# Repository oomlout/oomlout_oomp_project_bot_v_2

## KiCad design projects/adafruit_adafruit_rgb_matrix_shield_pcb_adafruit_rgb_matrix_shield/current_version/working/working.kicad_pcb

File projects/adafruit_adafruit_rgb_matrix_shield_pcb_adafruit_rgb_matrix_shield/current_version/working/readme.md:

# adafruit_rgb_matrix_shield_pcb
 
## summary 
* id: adafruit_adafruit_rgb_matrix_shield_pcb_adafruit_rgb_matrix_shield
* user: adafruit
* name: adafruit_rgb_matrix_shield_pcb
* board: adafruit_rgb_matrix_shield
* repo: https://github.com/adafruit/Adafruit-RGB-Matrix-Shield-PCB

* src_file_repo_sch: 
* src_file_repo_sch_link: https://github.com/adafruit/Adafruit-RGB-Matrix-Shield-PCB/tree/master/
* full details link: https://github.com/oomlout/oomlout_oomp_project_bot_v_2/tree/main/projects/adafruit_adafruit_rgb_matrix_shield_pcb_adafruit_rgb_matrix_shield/current_version/working  

## schematic  
  
[schematic (pdf)](working_schematic.pdf) 

## pcb  

[board (pdf)](working.pdf)  

## working_bom
| Id | Designator | Footprint | Quantity | Designation | Supplier and ref |  | None | 
| --- | --- | --- | --- | --- | --- | --- | --- | 
| 1 | SJ2,SJ6,SJ14,SJ13,SJ12,SJ10,SJ7,SJ3,SJ5,SJ4,SJ9,SJ8,SJ1 | SOLDERJUMPER_CLOSEDWIRE | 13 |  |  |  | [''] | 
| 2 | JP1,JP4 | 1X08-CLEANBIG | 2 |  |  |  | [''] | 
| 3 | U$9 | ADAFRUIT_TEXT_20MM | 1 |  |  |  | [''] | 
| 4 | S4 | B3F-10XX | 1 | 6mm |  |  | [''] | 
| 5 | JP15 | 2X08_SHROUDED | 1 | Shrouded 2x8 |  |  | [''] | 
| 6 | JP3,JP2 | 1X08_ROUND_76 | 2 |  |  |  | [''] | 
| 7 | @HOLE1,@HOLE0,@HOLE2 |  | 3 |  |  |  | [''] | 
| 8 | U$8 | PCBFEAT-REV-040 | 1 |  |  |  | [''] | 
| 9 | JP6 | 1X10_ROUND70 | 1 |  |  |  | [''] | 
| 10 | MATRIX_PWR0 | TERMBLOCK508 | 1 | PINHEAD |  |  | [''] | 
| 11 | U$41 | ARDUINOR3_ICSP_NODIM | 1 | ARDUINO_R3_ICSP_NODIM |  |  | [''] | 
| 12 | JP8 | 1X06-CLEANBIG | 1 |  |  |  | [''] | 

## bom_schematic
| Ref | Qnty | Value | Cmp name | Footprint | Description | Vendor | DNP | 
| --- | --- | --- | --- | --- | --- | --- | --- | 
| JP1, JP4 | 2 | PINHD-1X8CLEANBIG | PINHD-1X8CLEANBIG | working:1X08-CLEANBIG |  |  |  | 
| JP2, JP3 | 2 | HEADER-1X876MIL | HEADER-1X876MIL | working:1X08_ROUND_76 |  |  |  | 
| JP6 | 1 | HEADER-1X1070MIL | HEADER-1X1070MIL | working:1X10_ROUND70 |  |  |  | 
| JP8 | 1 | PINHD-1X6CB | PINHD-1X6CB | working:1X06-CLEANBIG |  |  |  | 
| JP15 | 1 | Shrouded 2x8 | HEADER-2X8_SHROUDED | working:2X08_SHROUDED |  |  |  | 
| MATRIX_PWR0 | 1 | PINHEAD | PINHEAD | working:TERMBLOCK508 |  |  |  | 
| S4 | 1 | 6mm | 10-XX | working:B3F-10XX |  |  |  | 
| SJ1, SJ2, SJ3, SJ4, SJ5, SJ6, SJ7, SJ8, SJ9, SJ10, SJ12, SJ13, SJ14 | 13 | SOLDERJUMPERCLOSED | SOLDERJUMPERCLOSED | working:SOLDERJUMPER_CLOSEDWIRE |  |  |  | 
| U$41 | 1 | ARDUINO_R3_ICSP_NODIM | ARDUINO_R3_ICSP_NODIM | working:ARDUINOR3_ICSP_NODIM |  |  |  |

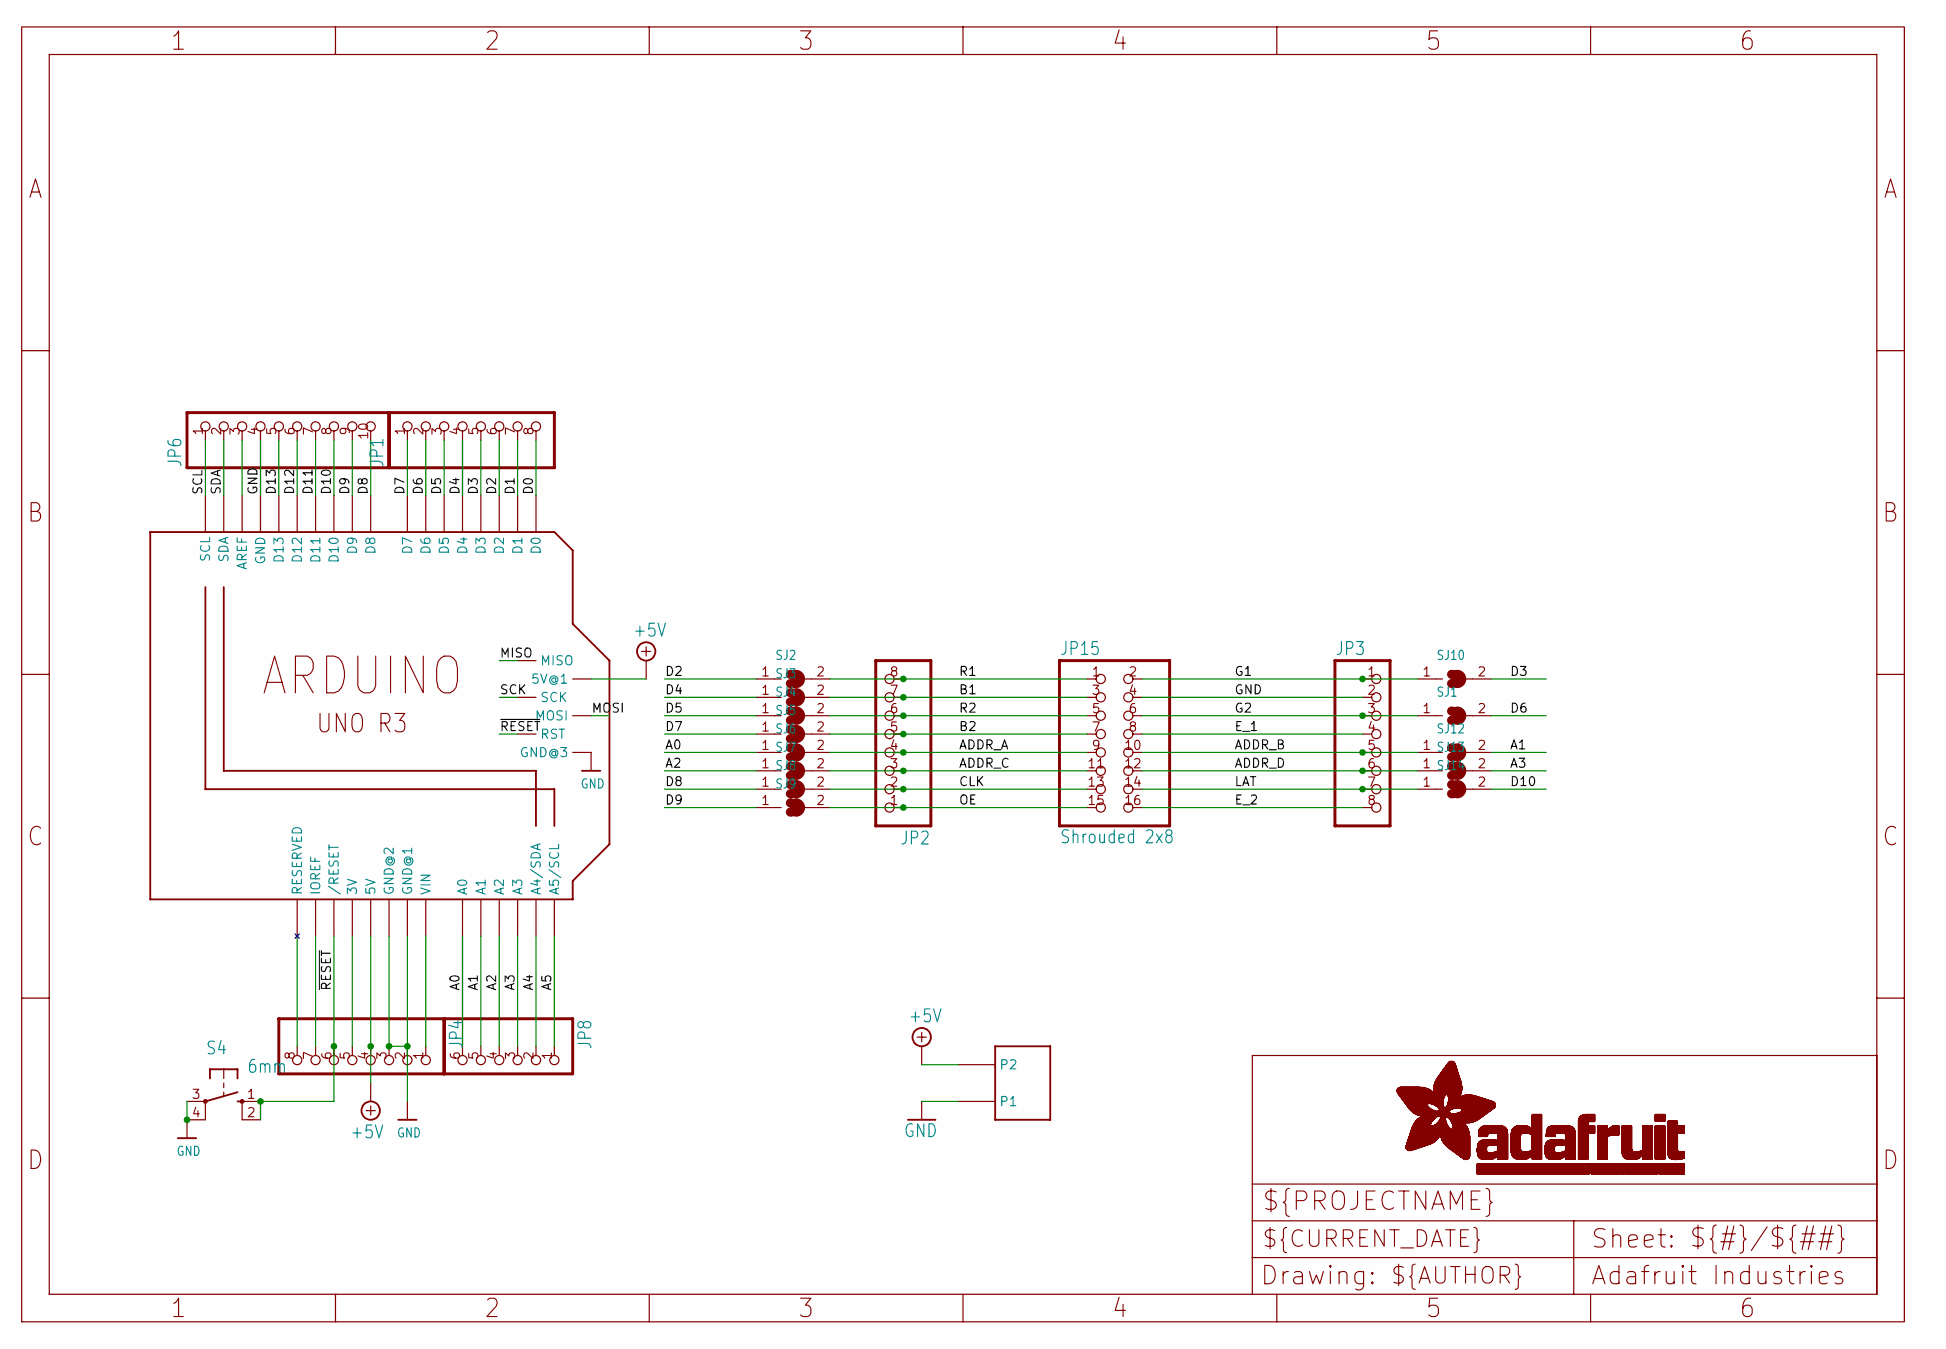
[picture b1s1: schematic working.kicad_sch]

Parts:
JP1, JP4: PINHD-1X8CLEANBIG; 1X08-CLEANBIG
JP2, JP3: HEADER-1X876MIL; 1X08_ROUND_76
JP6: HEADER-1X1070MIL; 1X10_ROUND70
JP8: PINHD-1X6CB; 1X06-CLEANBIG
JP15: Shrouded 2x8; 2X08_SHROUDED
MATRIX_PWR0: PINHEAD; TERMBLOCK508
S4: 6mm; B3F-10XX
SJ1, SJ2, SJ3, SJ4, SJ5, SJ6, SJ7, SJ8, SJ9, SJ10, SJ12, SJ13, SJ14: SOLDERJUMPERCLOSED; SOLDERJUMPER_CLOSEDWIRE
U$41: ARDUINO_R3_ICSP_NODIM; ARDUINOR3_ICSP_NODIM

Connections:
+3V: JP4.5, U$41.3V
+5V: JP4.4, MATRIX_PWR0.P$4 (P2), U$41.5V, U$41.5V_ICSP (5V@1)
A0: JP8.6, SJ6.1, U$41.A0
A1: JP8.5, SJ12.2, U$41.A1
A2: JP8.4, SJ7.1, U$41.A2
A3: JP8.3, SJ13.2, U$41.A3
A4: JP8.2, U$41.A4 (A4/SDA)
A5: JP8.1, U$41.A5 (A5/SCL)
ADDR_A: JP2.4, JP15.9, SJ6.2
ADDR_B: JP3.5, JP15.10, SJ12.1
ADDR_C: JP2.3, JP15.11, SJ7.2
ADDR_D: JP3.6, JP15.12, SJ13.1
AREF: JP6.3, U$41.AREF
B1: JP2.7, JP15.3, SJ3.2
B2: JP2.5, JP15.7, SJ5.2
CLK: JP2.2, JP15.13, SJ8.2
D0: JP1.8, U$41.D0
D1: JP1.7, U$41.D1
D2: JP1.6, SJ2.1, U$41.D2
D3: JP1.5, SJ10.2, U$41.D3
D4: JP1.4, SJ3.1, U$41.D4
D5: JP1.3, SJ4.1, U$41.D5
D6: JP1.2, SJ1.2, U$41.D6
D7: JP1.1, SJ5.1, U$41.D7
D8: JP6.10, SJ8.1, U$41.D8
D9: JP6.9, SJ9.1, U$41.D9
D10: JP6.8, SJ14.2, U$41.D10
D11: JP6.7, U$41.D11
D12: JP6.6, U$41.D12
D13: JP6.5, U$41.D13
E_1: JP3.4, JP15.8
E_2: JP3.8, JP15.16
G1: JP3.1, JP15.2, SJ10.1
G2: JP3.3, JP15.6, SJ1.1
GND: JP3.2, JP4.2, JP4.3, JP6.4, JP15.4, MATRIX_PWR0.P$3 (P1), S4.3, S4.4 (P1), U$41.GND, U$41.GND@1 (GND@2), U$41.GND@2 (GND@3), U$41.GND@3 (GND@1)
IOREF: JP4.7, U$41.IOREF
LAT: JP3.7, JP15.14, SJ14.1
MISO: U$41.MISO
MOSI: U$41.MOSI
NC: JP4.8, U$41.RESERVED
OE: JP2.1, JP15.15, SJ9.2
R1: JP2.8, JP15.1, SJ2.2
R2: JP2.6, JP15.5, SJ4.2
SCK: U$41.SCK
SCL: JP6.1, U$41.SCL
SDA: JP6.2, U$41.SDA
VIN: JP4.1, U$41.VIN
~RESET: JP4.6, S4.1 (S), S4.2 (S1), U$41.RESET (/RESET), U$41.RESET_ICSP (RST)

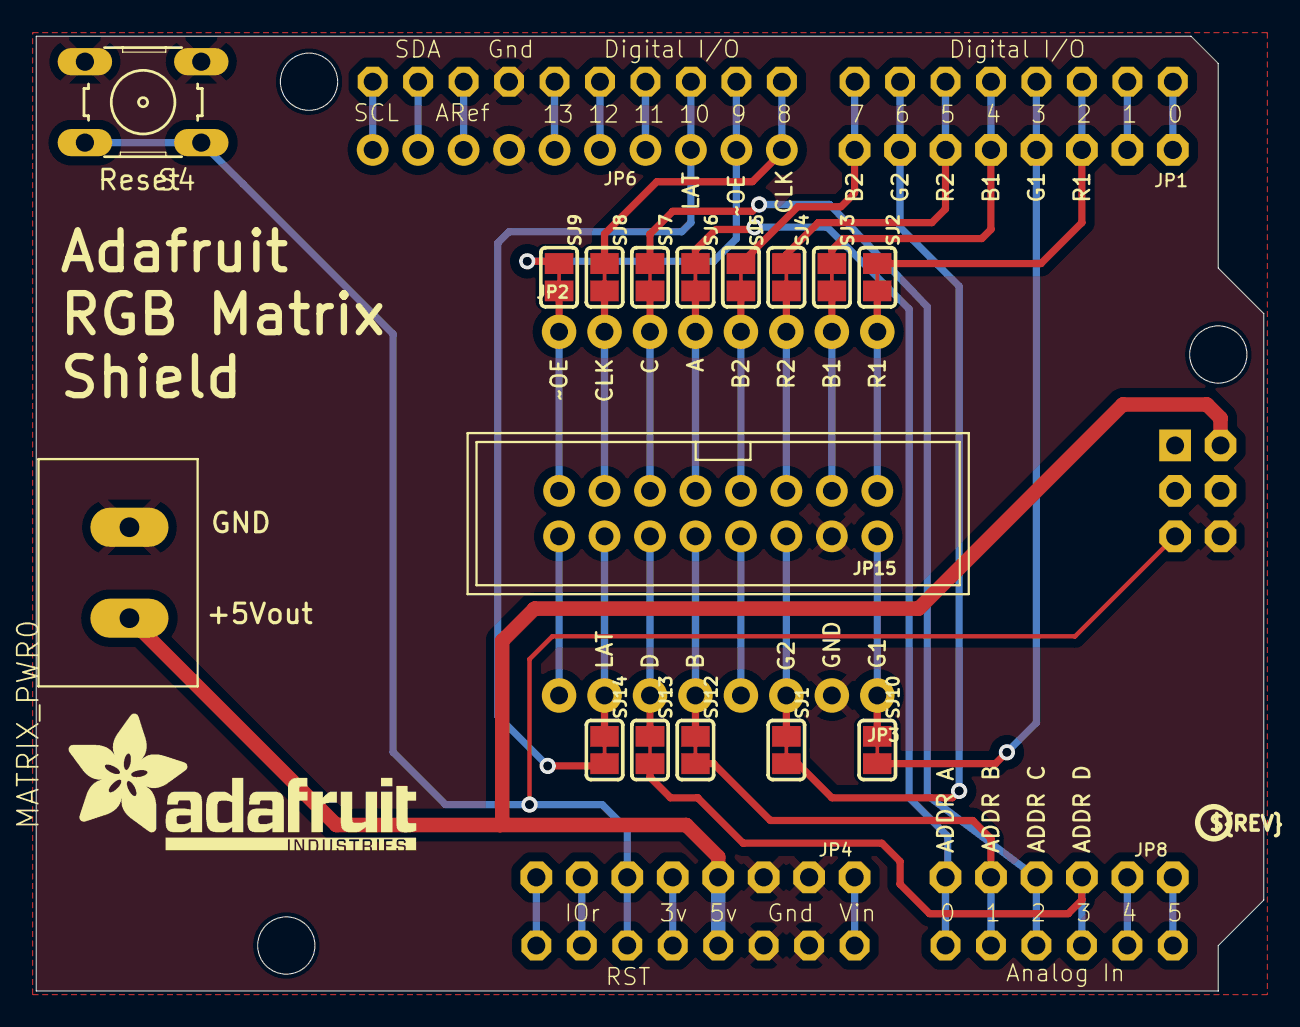
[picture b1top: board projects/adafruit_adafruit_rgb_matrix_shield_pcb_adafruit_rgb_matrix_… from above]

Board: 2 copper layers, 68.6 x 53.3 mm, 28 parts (0 on the bottom side), 45 nets.

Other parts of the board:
@HOLE0, @HOLE1, @HOLE2: (no value)
U$8: PCBFEAT-REV-040
U$9: ADAFRUIT_TEXT_20MM

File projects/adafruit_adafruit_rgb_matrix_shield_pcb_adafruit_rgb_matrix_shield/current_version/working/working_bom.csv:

"Id";"Designator";"Footprint";"Quantity";"Designation";"Supplier and ref";
1;"SJ2,SJ6,SJ14,SJ13,SJ12,SJ10,SJ7,SJ3,SJ5,SJ4,SJ9,SJ8,SJ1";"SOLDERJUMPER_CLOSEDWIRE";13;"";;;
2;"JP1,JP4";"1X08-CLEANBIG";2;"";;;
3;"U$9";"ADAFRUIT_TEXT_20MM";1;"";;;
4;"S4";"B3F-10XX";1;"6mm";;;
5;"JP15";"2X08_SHROUDED";1;"Shrouded 2x8";;;
6;"JP3,JP2";"1X08_ROUND_76";2;"";;;
7;"@HOLE1,@HOLE0,@HOLE2";"";3;"";;;
8;"U$8";"PCBFEAT-REV-040";1;"";;;
9;"JP6";"1X10_ROUND70";1;"";;;
10;"MATRIX_PWR0";"TERMBLOCK508";1;"PINHEAD";;;
11;"U$41";"ARDUINOR3_ICSP_NODIM";1;"ARDUINO_R3_ICSP_NODIM";;;
12;"JP8";"1X06-CLEANBIG";1;"";;;

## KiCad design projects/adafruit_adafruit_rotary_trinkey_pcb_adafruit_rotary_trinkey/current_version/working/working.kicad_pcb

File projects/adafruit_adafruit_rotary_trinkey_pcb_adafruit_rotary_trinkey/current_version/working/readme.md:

# adafruit_rotary_trinkey_pcb
 
## summary 
* id: adafruit_adafruit_rotary_trinkey_pcb_adafruit_rotary_trinkey
* user: adafruit
* name: adafruit_rotary_trinkey_pcb
* board: adafruit_rotary_trinkey
* repo: https://github.com/adafruit/Adafruit-Rotary-Trinkey-PCB

* src_file_repo_sch: 
* src_file_repo_sch_link: https://github.com/adafruit/Adafruit-Rotary-Trinkey-PCB/tree/main/
* full details link: https://github.com/oomlout/oomlout_oomp_project_bot_v_2/tree/main/projects/adafruit_adafruit_rotary_trinkey_pcb_adafruit_rotary_trinkey/current_version/working  

## schematic  
  
[schematic (pdf)](working_schematic.pdf) 

## pcb  

[board (pdf)](working.pdf)  

## working_bom
| Id | Designator | Footprint | Quantity | Designation | Supplier and ref |  | None | 
| --- | --- | --- | --- | --- | --- | --- | --- | 
| 1 | SW1 | PEC11+SWITCH | 1 | PEC11 |  |  | [''] | 
| 2 | CN1 | USBA_PCB | 1 |  |  |  | [''] | 
| 3 | TOUCH0 | TESTPOINT_PAD_1MM | 1 |  |  |  | [''] | 
| 4 | LED1 | SK6805_1515 | 1 | WS2812B_SK6805_1515 |  |  | [''] | 
| 5 | Q2 | BTN_KMR2_4.6X2.8 | 1 | reset |  |  | [''] | 
| 6 | C8,C3 | 0805-NO | 2 | 10uF |  |  | [''] | 
| 7 | IC3 | QFN32_5MM | 1 | ATSAMD21E |  |  | [''] | 
| 8 | RST0,SWD0,SWC0 | TP16R | 3 | TPTP16R |  |  | [''] | 
| 9 | U$5 | ADAFRUIT_9MM | 1 |  |  |  | [''] | 
| 10 | FID2,FID1 | FIDUCIAL_1MM | 2 | FIDUCIAL_1MM |  |  | [''] | 
| 11 | C4,C5 | 0603-NO | 2 | 1uF |  |  | [''] | 
| 12 | U$8 | PCBFEAT-REV-040 | 1 |  |  |  | [''] | 
| 13 | U1 | SOT23-5 | 1 | AP2112K-3.3 |  |  | [''] | 

## bom_schematic
| Ref | Qnty | Value | Cmp name | Footprint | Description | Vendor | DNP | 
| --- | --- | --- | --- | --- | --- | --- | --- | 
| C3, C8 | 2 | 10uF | CAP_CERAMIC0805-NOOUTLINE | working:0805-NO |  |  |  | 
| C4, C5 | 2 | 1uF | CAP_CERAMIC0603_NO | working:0603-NO |  |  |  | 
| CN1 | 1 | USB_TYPEAPCB | USB_TYPEAPCB | working:USBA_PCB |  |  |  | 
| FID1, FID2 | 2 | FIDUCIAL_1MM | FIDUCIAL_1MM | working:FIDUCIAL_1MM |  |  |  | 
| IC3 | 1 | ATSAMD21E | ATSAMD21E | working:QFN32_5MM |  |  |  | 
| LED1 | 1 | WS2812B_SK6805_1515 | WS2812B_SK6805_1515 | working:SK6805_1515 |  |  |  | 
| Q2 | 1 | reset | SWITCH_TACT_SMT4.6X2.8 | working:BTN_KMR2_4.6X2.8 |  |  |  | 
| RST0 | 1 | TPTP16R | TPTP16R | working:TP16R |  |  |  | 
| SW1 | 1 | PEC11 | ENCODER_PLUS_SWITCH_PEC11 | working:PEC11+SWITCH |  |  |  | 
| SWC0 | 1 | TPTP16R | TPTP16R | working:TP16R |  |  |  | 
| SWD0 | 1 | TPTP16R | TPTP16R | working:TP16R |  |  |  | 
| TOUCH0 | 1 | TESTPOINTPAD1MM | TESTPOINTPAD1MM | working:TESTPOINT_PAD_1MM |  |  |  | 
| U1 | 1 | AP2112K-3.3 | VREG_SOT23-5 | working:SOT23-5 |  |  |  |

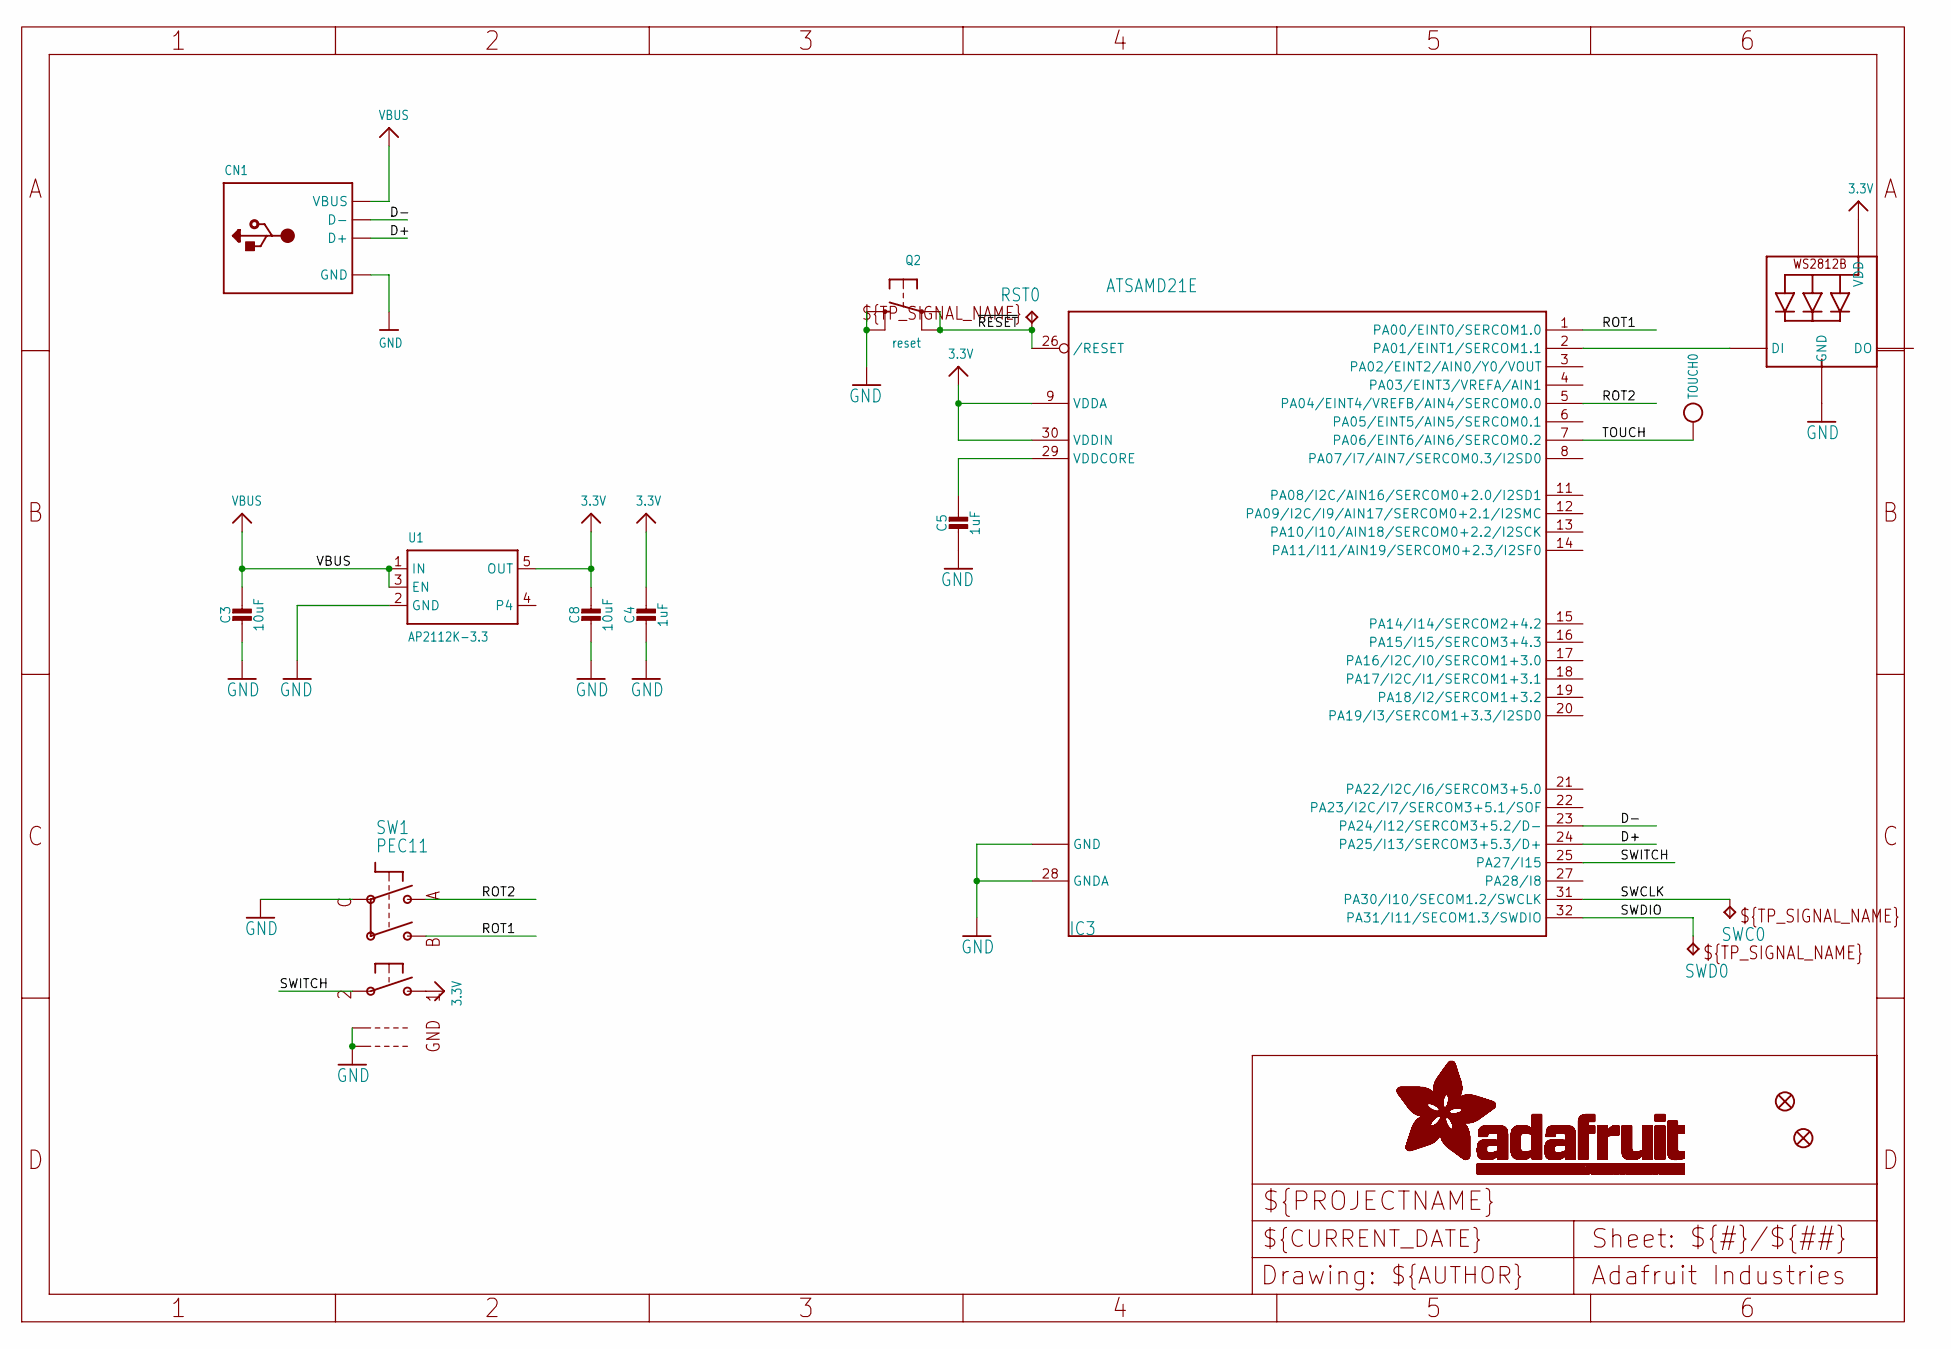
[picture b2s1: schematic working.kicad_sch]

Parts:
C3, C8: 10uF; 0805-NO
C4, C5: 1uF; 0603-NO
CN1: USB_TYPEAPCB; USBA_PCB
FID1, FID2: FIDUCIAL_1MM
IC3: ATSAMD21E; QFN32_5MM
LED1: WS2812B_SK6805_1515; SK6805_1515
Q2: reset; BTN_KMR2_4.6X2.8
RST0: TPTP16R; TP16R
SW1: PEC11; PEC11+SWITCH
SWC0: TPTP16R; TP16R
SWD0: TPTP16R; TP16R
TOUCH0: TESTPOINTPAD1MM; TESTPOINT_PAD_1MM
U1: AP2112K-3.3; SOT23-5

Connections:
3.3V: C4.1, C8.1, IC3.9 (VDDA), IC3.30 (VDDIN), LED1.2 (VDD), SW1.P$1, U1.5 (OUT)
D+: CN1.USB_PLUS (D+), IC3.24 (PA25/I13/SERCOM3+5.3/D+)
D-: CN1.USB_NEG (D-), IC3.23 (PA24/I12/SERCOM3+5.2/D-)
GND: C3.2, C4.2, C5.2, C8.2, CN1.GND, IC3.10 (GND), IC3.28 (GNDA), IC3.33 (GND), LED1.4 (GND), Q2.B (S), Q2.B' (S1), SW1.P$C, SW1.P$GND1, SW1.P$GND2, U1.2 (GND)
unnamed: IC3.2 (PA01/EINT1/SERCOM1.1), LED1.1 (DI)
ROT1: IC3.1 (PA00/EINT0/SERCOM1.0), SW1.P$B
ROT2: IC3.5 (PA04/EINT4/VREFB/AIN4/SERCOM0.0), SW1.P$A
SWCLK: IC3.31 (PA30/I10/SECOM1.2/SWCLK), SWC0.TP
SWDIO: IC3.32 (PA31/I11/SECOM1.3/SWDIO), SWD0.TP
SWITCH: IC3.25 (PA27/I15), SW1.P$2
TOUCH: IC3.7 (PA06/EINT6/AIN6/SERCOM0.2), TOUCH0.P$1
VBUS: C3.1, CN1.VCC (VBUS), U1.1 (IN), U1.3 (EN)
VDDCORE1: C5.1, IC3.29 (VDDCORE)
~RESET: IC3.26 (/RESET), Q2.A, Q2.A' (P1), RST0.TP

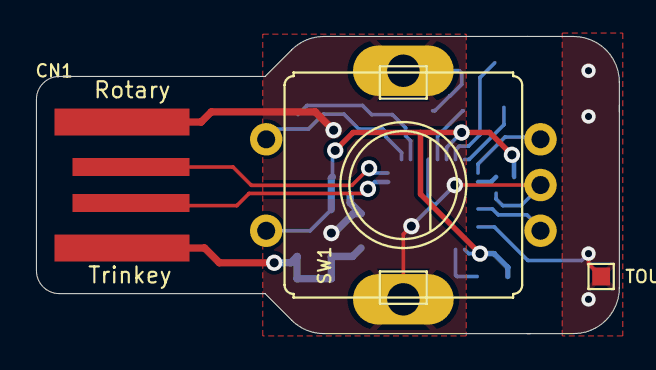
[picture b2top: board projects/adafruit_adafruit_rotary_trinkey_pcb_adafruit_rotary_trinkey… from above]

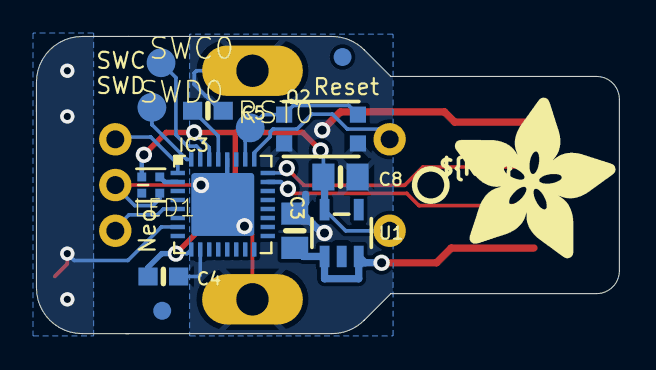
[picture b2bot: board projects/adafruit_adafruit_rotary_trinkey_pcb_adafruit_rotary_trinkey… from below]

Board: 2 copper layers, 32.4 x 16.5 mm, 18 parts (15 on the bottom side), 14 nets.

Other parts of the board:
U$5: ADAFRUIT_9MM
U$8: PCBFEAT-REV-040

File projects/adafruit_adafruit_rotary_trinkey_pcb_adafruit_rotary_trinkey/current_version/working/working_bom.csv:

"Id";"Designator";"Footprint";"Quantity";"Designation";"Supplier and ref";
1;"SW1";"PEC11+SWITCH";1;"PEC11";;;
2;"CN1";"USBA_PCB";1;"";;;
3;"TOUCH0";"TESTPOINT_PAD_1MM";1;"";;;
4;"LED1";"SK6805_1515";1;"WS2812B_SK6805_1515";;;
5;"Q2";"BTN_KMR2_4.6X2.8";1;"reset";;;
6;"C8,C3";"0805-NO";2;"10uF";;;
7;"IC3";"QFN32_5MM";1;"ATSAMD21E";;;
8;"RST0,SWD0,SWC0";"TP16R";3;"TPTP16R";;;
9;"U$5";"ADAFRUIT_9MM";1;"";;;
10;"FID2,FID1";"FIDUCIAL_1MM";2;"FIDUCIAL_1MM";;;
11;"C4,C5";"0603-NO";2;"1uF";;;
12;"U$8";"PCBFEAT-REV-040";1;"";;;
13;"U1";"SOT23-5";1;"AP2112K-3.3";;;

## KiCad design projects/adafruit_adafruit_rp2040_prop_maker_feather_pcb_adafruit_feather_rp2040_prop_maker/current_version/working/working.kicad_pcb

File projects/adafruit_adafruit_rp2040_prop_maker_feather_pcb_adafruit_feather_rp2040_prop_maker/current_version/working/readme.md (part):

# adafruit_rp2040_prop_maker_feather_pcb
 
## summary 
* id: adafruit_adafruit_rp2040_prop_maker_feather_pcb_adafruit_feather_rp2040_prop_maker
* user: adafruit
* name: adafruit_rp2040_prop_maker_feather_pcb
* board: adafruit_feather_rp2040_prop_maker
* repo: https://github.com/adafruit/Adafruit-RP2040-Prop-Maker-Feather-PCB

* src_file_repo_sch: 
* src_file_repo_sch_link: https://github.com/adafruit/Adafruit-RP2040-Prop-Maker-Feather-PCB/tree/main/
* full details link: https://github.com/oomlout/oomlout_oomp_project_bot_v_2/tree/main/projects/adafruit_adafruit_rp2040_prop_maker_feather_pcb_adafruit_feather_rp2040_prop_maker/current_version/working  

## schematic  
  
[schematic (pdf)](working_schematic.pdf) 

## pcb  

[board (pdf)](working.pdf)  

## working_bom
| Id | Designator | Footprint | Quantity | Designation | Supplier and ref |  | None | 
| --- | --- | --- | --- | --- | --- | --- | --- | 
| 1 | PLABEL30 | PLABEL30 | 1 |  |  |  | [''] | 
| 2 | R2,R5,R1,R4,R14,R3,R15,R7 | _0402NO | 8 | 10K |  |  | [''] | 
| 3 | C7,C6,C12,C18,C9,C13,C16,C14 | _0402NO | 8 | 0.1uF |  |  | [''] | 
| 4 | R6,R11 | _0402NO | 2 | 1K |  |  | [''] | 
| 5 | U$31,U$32 | MOUNTINGHOLE_2.5_PLATED | 2 | MOUNTINGHOLE2.5 |  |  | [''] | 
| 6 | C20,C1,C19,C5,C4 | 0805-NO | 5 | 10uF/16V |  |  | [''] | 
| 7 | PLABEL72 | PLABEL72 | 1 |  |  |  | [''] | 
| 8 | U$35,U$34 | FIDUCIAL_1MM | 2 | FIDUCIAL_1MM |  |  | [''] | 
| 9 | OUTPUTS0 | 1X06_OVAL | 1 | TERMINALS |  |  | [''] | 
| 10 | PLABEL13 | PLABEL13 | 1 |  |  |  | [''] | 
| 11 | LED1 | SK6805_1515 | 1 | WS2812B_SK6805_1515 |  |  | [''] | 
| 12 | PLABEL73 | PLABEL73 | 1 |  |  |  | [''] | 
| 13 | R19 | _0402NO | 1 | 100 |  |  | [''] | 
| 14 | PLABEL6 | PLABEL6 | 1 |  |  |  | [''] | 
| 15 | Y1 | CRYSTAL_2.5X2 | 1 | 12MHz/12pF |  |  | [''] | 
| 16 | PLABEL33 | PLABEL33 | 1 |  |  |  | [''] | 
| 17 | U2 | SOT23-5 | 1 | RT9080-3.3 |  |  | [''] | 
| 18 | R16,R17 | _0402NO | 2 | 100K |  |  | [''] | 
| 19 | PLABEL19,PLABEL26 | PLABEL26 | 2 |  |  |  | [''] | 
| 20 | PLABEL36 | PLABEL36 | 1 |  |  |  | [''] | 
| 21 | PLABEL23 | PLABEL23 | 1 |  |  |  | [''] | 
| 22 | C2,C3 | _0402NO | 2 | 22pF |  |  | [''] | 
| 23 | C10,C11,C15,C8,C17 | _0402NO | 5 | 1uF/25V |  |  | [''] | 
| 24 | SERVO0 | 1X03_ROUND_76 | 1 | 1x3M |  |  | [''] | 
| 25 | IC1 | QFN56_7MM_REDUCEDEPAD | 1 | RP2040_QFN56 |  |  | [''] | 
| 26 | R12,R8,R13 | _0402NO | 3 | 5.1K |  |  | [''] | 
| 27 | PLABEL18 | PLABEL18 | 1 |  |  |  | [''] | 
| 28 | R18 | _0402NO | 1 | 1M |  |  | [''] | 
| 29 | PLABEL5 | PLABEL5 | 1 |  |  |  | [''] | 
| 30 | @HOLE1,@HOLE0 |  | 2 |  |  |  | [''] | 
| 31 | PLABEL16 | PLABEL16 | 1 |  |  |  | [''] | 
| 32 | PLABEL3 | PLABEL3 | 1 |  |  |  | [''] | 
| 33 | PLABEL4 | PLABEL4 | 1 |  |  |  | [''] | 
| 34 | U3 | SOT23-5 | 1 | MCP73831T-2ACI/OT |  |  | [''] | 
| 35 | PLABEL27 | PLABEL27 | 1 |  |  |  | [''] | 
| 36 | PLABEL17 | PLABEL17 | 1 |  |  |  | [''] | 
| 37 | IC4 | LGA16_3X3MM | 1 | LIS3DH |  |  | [''] | 
| 38 | R10,R9 | _0402NO | 2 | 22 ohm |  |  | [''] | 
| 39 | C22,C21 | _0402NO | 2 | 220pF |  |  | [''] | 
| 40 | PLABEL22 | PLABEL22 | 1 |  |  |  | [''] | 
| 41 | U4 | QFN16_3MM | 1 | MAX98357A |  |  | [''] | 
| 42 | X6 | USB_C_CUSB31-CFM2AX-01-X | 1 | USB Type C |  |  | [''] | 
| 43 | PLABEL71 | PLABEL71 | 1 |  |  |  | [''] | 
| 44 | L0 | CHIPLED_0603_NOOUTLINE | 1 | RED |  |  | [''] | 
| 45 | PLABEL21 | PLABEL21 | 1 |  |  |  | [''] | 
| 46 | PLABEL31 | PLABEL31 | 1 |  |  |  | [''] | 
| 47 | PLABEL7 | PLABEL7 | 1 |  |  |  | [''] | 
| 48 | PLABEL12 | PLABEL12 | 1 |  |  |  | [''] | 
| 49 | PLABEL8 | PLABEL8 | 1 |  |  |  | [''] | 
| 50 | Q2 | SOT23-WIDE | 1 | C20917 |  |  | [''] | 
| 51 | PLABEL9 | PLABEL9 | 1 |  |  |  | [''] | 
| 52 | Q1 | SOT23-WIDE | 1 | AO3401 |  |  | [''] | 
| 53 | Q3 | DFN2015-3 | 1 | DMG3415UFY |  |  | [''] | 
| 54 | FB2,FB1 | 0603-NO | 2 | Ferrite |  |  | [''] | 
| 55 | PLABEL2 | PLABEL2 | 1 |  |  |  | [''] | 
| 56 | PLABEL24 | PLABEL24 | 1 |  |  |  | [''] | 
| 57 | PLABEL11 | PLABEL11 | 1 |  |  |  | [''] | 
| 58 | SW2,SW1 | BTN_RKB2_4.6X2.8 | 2 | RKB2 |  |  | [''] | 
| 59 | U1 | USON8_4X4 | 1 | 8MB QSPI |  |  | [''] | 
| 60 | PLABEL10 | PLABEL10 | 1 |  |  |  | [''] | 
| 61 | PLABEL28 | PLABEL28 | 1 |  |  |  | [''] | 
| 62 | X1 | JSTPH2_BATT | 1 | JSTPH |  |  | [''] | 
| 63 | PLABEL29 | PLABEL29 | 1 |  |  |  | [''] | 
| 64 | U$42 | ADAFRUIT_3.5MM | 1 |  |  |  | [''] | 
| 65 | PLABEL14 | PLABEL14 | 1 |  |  |  | [''] | 
| 66 | CONN1 | JST_SH4_RA | 1 | STEMMA_I2C_QTRA |  |  | [''] | 
| 67 | JP3 | 1X12_ROUND | 1 |  |  |  | [''] | 
| 68 | D3 | SOD-323_MINI | 1 | 1N4148 |  |  | [''] | 
| 69 | D4 | SOD-323F | 1 | PMEG2020AEA |  |  | [''] | 
| 70 | PLABEL1 | PLABEL1 | 1 |  |  |  | [''] | 
| 71 | IC2 | SC70-5 | 1 | 74AHCT1G125DCK |  |  | [''] | 
| 72 | PLABEL25 | PLABEL25 | 1 |  |  |  | [''] | 
| 73 | JP1 | 1X16_ROUND | 1 |  |  |  | [''] | 
| 74 | PLABEL70 | PLABEL70 | 1 |  |  |  | [''] | 
| 75 | PLABEL32 | PLABEL32 | 1 |  |  |  | [''] | 
| 76 | PLABEL15 | PLABEL15 | 1 |  |  |  | [''] | 
| 77 | PLABEL0 | PLABEL0 | 1 |  |  |  | [''] | 
| 78 | CHG0 | CHIPLED_0603_NOOUTLINE | 1 | ORANGE |  |  | [''] | 
| 79 | PLABEL81 | PLABEL81 | 1 |  |  |  | [''] | 
| 80 | PLABEL88 | PLABEL88 | 1 |  |  |  | [''] | 
| 81 | PLABEL47 | PLABEL47 | 1 |  |  |  | [''] | 
| 82 | PLABEL75 | PLABEL75 | 1 |  |  |  | [''] | 
| 83 | PLABEL69 | PLABEL69 | 1 |  |  |  | [''] | 
| 84 | PLABEL50 | PLABEL50 | 1 |  |  |  | [''] | 
| 85 | PLABEL40 | PLABEL40 | 1 |  |  |  | [''] | 
| 86 | PLABEL51 | PLABEL51 | 1 |  |  |  | [''] | 
| 87 | PLABEL42 | PLABEL42 | 1 |  |  |  | [''] | 
| 88 | PLABEL46 | PLABEL46 | 1 |  |  |  | [''] | 
| 89 | PLABEL86 | PLABEL86 | 1 |  |  |  | [''] | 
| 90 | PLABEL60 | PLABEL60 | 1 |  |  |  | [''] | 
| 91 | U$13 | PCBFEAT-REV-040 | 1 |  |  |  | [''] | 
| 92 | D+1,D-1 | B1,27 | 2 | TPB1,27 |  |  | [''] | 
| 93 | PLABEL38 | PLABEL38 | 1 |  |  |  | [''] | 
| 94 | PLABEL58 | PLABEL58 | 1 |  |  |  | [''] | 
| 95 | PLABEL55 | PLABEL55 | 1 |  |  |  | [''] | 
| 96 | PLABEL85 | PLABEL85 | 1 |  |  |  | [''] | 
| 97 | PLABEL59 | PLABEL59 | 1 |  |  |  | [''] | 
| 98 | GAIN0 | SOLDERJUMPER_2WAY_OPEN_NOPASTE | 1 |  |  |  | [''] | 
| 99 | PLABEL82 | PLABEL82 | 1 |  |  |  | [''] | 
| 100 | PLABEL80 | PLABEL80 | 1 |  |  |  | [''] | 
| 101 | PLABEL57 | PLABEL57 | 1 |  |  |  | [''] | 
| 102 | PLABEL45 | PLABEL45 | 1 |  |  |  | [''] | 
| 103 | PLABEL48 | PLABEL48 | 1 |  |  |  | [''] | 
| 104 | PLABEL52 | PLABEL52 | 1 |  |  |  | [''] | 
| 105 | PLABEL77 | PLABEL77 | 1 |  |  |  | [''] | 
| 106 | TP3 | TESTPOINT_ROUND_1.5MM_NO | 1 |  |  |  | [''] | 
| 107 | PLABEL43 | PLABEL43 | 1 |  |  |  | [''] | 
| 108 | PLABEL53 | PLABEL53 | 1 |  |  |  | [''] | 
| 109 | PLABEL62 | PLABEL62 | 1 |  |  |  | [''] | 
| 110 | PLABEL83 | PLABEL83 | 1 |  |  |  | [''] | 
| 111 | PLABEL74 | PLABEL74 | 1 |  |  |  | [''] | 
| 112 | PLABEL41 | PLABEL41 | 1 |  |  |  | [''] | 
| 113 | PLABEL56 | PLABEL56 | 1 |  |  |  | [''] | 
| 114 | PLABEL76 | PLABEL76 | 1 |  |  |  | [''] | 
| 115 | PLABEL61 | PLABEL61 | 1 |  |  |  | [''] | 
| 116 | PLABEL78 | PLABEL78 | 1 |  |  |  | [''] | 
| 117 | PLABEL89 | PLABEL89 | 1 |  |  |  | [''] | 
| 118 | PLABEL37 | PLABEL37 | 1 |  |  |  | [''] | 
| 119 | PLABEL68 | PLABEL68 | 1 |  |  |  | [''] | 
| 120 | PLABEL39 | PLABEL39 | 1 |  |  |  | [''] | 
| 121 | PLABEL84 | PLABEL84 | 1 |  |  |  | [''] | 
| 122 | PLABEL54 | PLABEL54 | 1 |  |  |  | [''] | 
| 123 | PLABEL87 | PLABEL87 | 1 |  |  |  | [''] | 
| 124 | PLABEL63 | PLABEL63 | 1 |  |  |  | [''] | 
| 125 | PLABEL79 | PLABEL79 | 1 |  |  |  | [''] | 
| 126 | PLABEL49 | PLABEL49 | 1 |  |  |  | [''] | 
| 127 | PLABEL44 | PLABEL44 | 1 |  |  |  | [''] | 
| 128 | CHG_EN0 | SOLDERJUMPER_CLOSEDWIRE | 1 |  |  |  | [''] | 

## bom_schematic
| Ref | Qnty | Value | Cmp name | Footprint | Description | Vendor | DNP | 
| --- | --- | --- | --- | --- | --- | --- | --- | 
| C1, C4, C5, C19, C20 | 5 | 10uF/16V | CAP_CERAMIC0805-NOOUTLINE | working:0805-NO |  |  |  | 
| C2, C3 | 2 | 22pF | CAP_CERAMIC_0402NO | working:_0402NO |  |  |  | 
| C6, C7, C9, C12, C13, C14, C16, C18 | 8 | 0.1uF | CAP_CERAMIC_0402NO | working:_0402NO |  |  |  | 
| C8, C10, C11, C15, C17 | 5 | 1uF/25V | CAP_CERAMIC_0402NO | working:_0402NO |  |  |  | 
| C21, C22 | 2 | 220pF | CAP_CERAMIC_0402NO | working:_0402NO |  |  |  | 
| CHG0 | 1 | ORANGE | LED0603_NOOUTLINE | working:CHIPLED_0603_NOOUTLINE |  |  |  | 
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
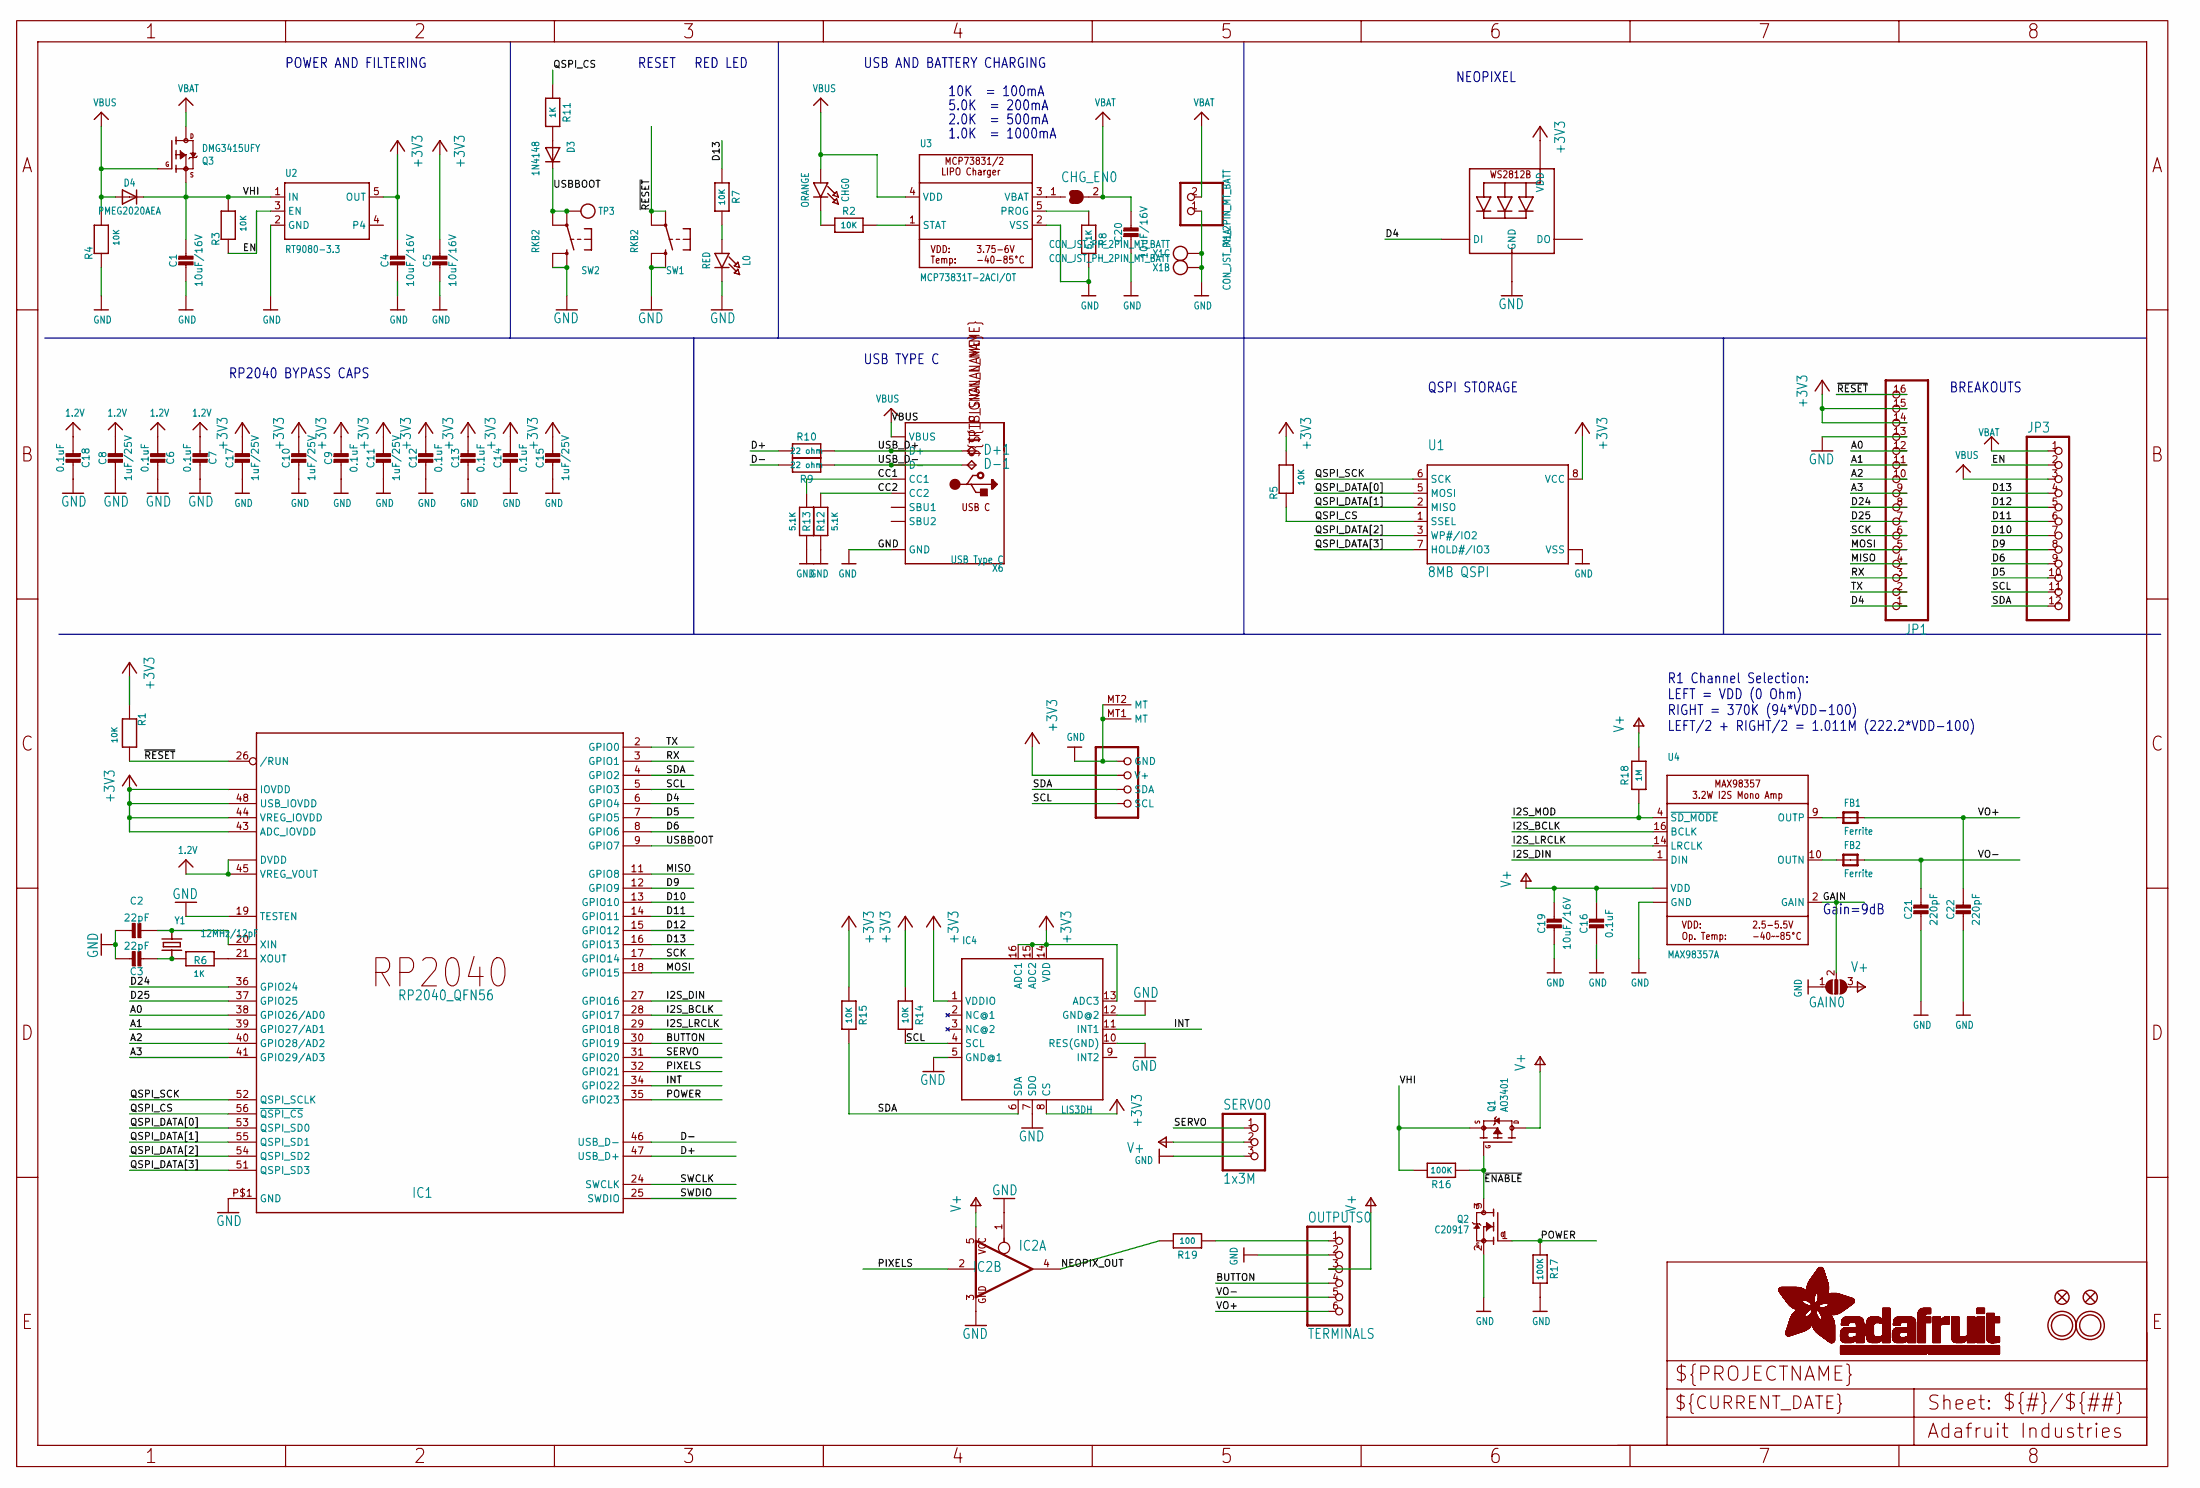
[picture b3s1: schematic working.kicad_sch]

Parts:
C1, C4, C5, C19, C20: 10uF/16V; 0805-NO
C2, C3: 22pF; _0402NO
C6, C7, C9, C12, C13, C14, C16, C18: 0.1uF; _0402NO
C8, C10, C11, C15, C17: 1uF/25V; _0402NO
C21, C22: 220pF; _0402NO
CHG0: ORANGE; CHIPLED_0603_NOOUTLINE
CHG_EN0: SOLDERJUMPER_CLOSED; SOLDERJUMPER_CLOSEDWIRE
CONN1: STEMMA_I2C_QTRA; JST_SH4_RA
D3: 1N4148; SOD-323_MINI
D4: PMEG2020AEA; SOD-323F
D+1: TPB1,27; B1,27
D-1: TPB1,27; B1,27
FB1, FB2: Ferrite; 0603-NO
GAIN0: SOLDERJUMPER_2WAY; SOLDERJUMPER_2WAY_OPEN_NOPASTE
IC1: RP2040_QFN56; QFN56_7MM_REDUCEDEPAD
IC2: 741G125DCK; SC70-5
IC4: LIS3DH; LGA16_3X3MM
JP1: HEADER-1X16ROUND; 1X16_ROUND
JP3: HEADER-1X12; 1X12_ROUND
L0: RED; CHIPLED_0603_NOOUTLINE
LED1: WS2812B_SK6805_1515; SK6805_1515
OUTPUTS0: TERMINALS; 1X06_OVAL
Q1: AO3401; SOT23-WIDE
Q2: C20917; SOT23-WIDE
Q3: DMG3415UFY; DFN2015-3
R1, R2, R3, R4, R5, R7, R14, R15: 10K; _0402NO
R6, R11: 1K; _0402NO
R8, R12, R13: 5.1K; _0402NO
R9, R10: 22 ohm; _0402NO
R16, R17: 100K; _0402NO
R18: 1M; _0402NO
R19: 100; _0402NO
SERVO0: 1x3M; 1X03_ROUND_76
SW1, SW2: RKB2; BTN_RKB2_4.6X2.8
TP3: TESTPOINTROUND1.5MMNO; TESTPOINT_ROUND_1.5MM_NO
U1: 8MB QSPI; USON8_4X4
U2: RT9080-3.3; SOT23-5; JLC_ROTATION 0
U3: MCP73831T-2ACI/OT; SOT23-5; JLC_ROTATION 0
U4: MAX98357A; QFN16_3MM
U$31, U$32: MOUNTINGHOLE2.5; MOUNTINGHOLE_2.5_PLATED
U$34, U$35: FIDUCIAL_1MM
X1: CON_JST_PH_2PIN_MT_BATT; JSTPH2_BATT
X6: USB Type C; USB_C_CUSB31-CFM2AX-01-X
Y1: 12MHz/12pF; CRYSTAL_2.5X2

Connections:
1.2V: C6.2, C7.2, C8.1, C18.2, IC1.23 (DVDD), IC1.45 (VREG_VOUT), IC1.50 (DVDD)
+3V3: C4.1, C5.1, C9.1, C10.1, C11.1, C12.1, C13.1, C14.1, C15.1, C17.1, CONN1.2 (V+), IC1.1 (IOVDD), IC1.10 (IOVDD), IC1.22 (IOVDD), IC1.33 (IOVDD), IC1.42 (IOVDD), IC1.43 (ADC_IOVDD), IC1.44 (VREG_IOVDD), IC1.48 (USB_IOVDD), IC1.49 (IOVDD), IC4.1 (VDDIO), IC4.8 (CS), IC4.13 (ADC3), IC4.14 (VDD), IC4.15 (ADC2), IC4.16 (ADC1), JP1.14, JP1.15, LED1.2 (VDD), R1.1, R5.2, R14.1, R15.1, U1.8 (VCC), U2.5 (OUT)
A0: IC1.38 (GPIO26/AD0), JP1.12
A1: IC1.39 (GPIO27/AD1), JP1.11
A2: IC1.40 (GPIO28/AD2), JP1.10
A3: IC1.41 (GPIO29/AD3), JP1.9
BUTTON: IC1.30 (GPIO19), OUTPUTS0.4
CC1: R13.2, X6.A5 (CC1)
CC2: R12.2, X6.B5 (CC2)
D4: IC1.6 (GPIO4), JP1.1, LED1.1 (DI)
D5: IC1.7 (GPIO5), JP3.10
D6: IC1.8 (GPIO6), JP3.9
D9: IC1.12 (GPIO9), JP3.8
D10: IC1.13 (GPIO10), JP3.7
D11: IC1.14 (GPIO11), JP3.6
D12: IC1.15 (GPIO12), JP3.5
D13: IC1.16 (GPIO13), JP3.4, R7.1
D24: IC1.36 (GPIO24), JP1.8
D25: IC1.37 (GPIO25), JP1.7
D+: IC1.47 (USB_D+), R10.2
D-: IC1.46 (USB_D-), R9.2
EN: JP3.2, R3.1, U2.3 (EN)
GAIN: GAIN0.2, U4.2 (GAIN)
GND: C1.2, C2.1, C3.1, C4.2, C5.2, C6.1, C7.1, C8.2, C9.2, C10.2, C11.2, C12.2, C13.2, C14.2, C15.2, C16.2, C17.2, C18.1, C19.2, C20.2, C21.2, C22.2, CONN1.1 (GND), CONN1.MT1 (MT), CONN1.MT2 (MT), GAIN0.1, IC1.19 (TESTEN), IC1.P$1 (GND), IC2.1 (OE), IC2.3 (GND), IC4.5 (GND@1), IC4.7 (SDO), IC4.10 (RES(GND)), IC4.12 (GND@2), JP1.13, L0.C, LED1.4 (GND), OUTPUTS0.2, Q2.2 (S), R4.1, R8.2, R12.1, R13.1, R17.2, SERVO0.3, SW1.B (S), SW1.B' (S1), SW2.B (S), SW2.B' (S1), U1.4 (VSS), U1.PAD (VSS), U2.2 (GND), U3.2 (VSS), U4.3 (GND), U4.11 (GND), U4.15 (GND), U4.THERMAL (GND), X1.1, X1.NC1, X1.NC2, X6.A1B12 (GND), X6.B1A12 (GND)
I2S_BCLK: IC1.28 (GPIO17), U4.16 (BCLK)
I2S_DIN: IC1.27 (GPIO16), U4.1 (DIN)
I2S_LRCLK: IC1.29 (GPIO18), U4.14 (LRCLK)
I2S_MOD: R18.1, U4.4 (~SD_MODE)
INT: IC1.34 (GPIO22), IC4.11 (INT1)
MISO: IC1.11 (GPIO8), JP1.4
MOSI: IC1.18 (GPIO15), JP1.5
unnamed: CHG0.C, R2.1
unnamed: L0.A, R7.2
unnamed: R2.2, U3.1 (STAT)
unnamed: R8.1, U3.5 (PROG)
unnamed: C2.2, IC1.20 (XIN), Y1.3 (2)
unnamed: C3.2, R6.1, Y1.1
unnamed: IC1.21 (XOUT), R6.2
unnamed: FB2.1, U4.10 (OUTN)
unnamed: FB1.1, U4.9 (OUTP)
unnamed: CHG_EN0.1, U3.3 (VBAT)
unnamed: D3.A, R11.2
NEOPIX_OUT: IC2.4 (O), R19.2
PIXELOUT: OUTPUTS0.1, R19.1
PIXELS: IC1.32 (GPIO21), IC2.2 (I)
POWER: IC1.35 (GPIO23), Q2.1 (G), R17.1
QSPI_CS: IC1.56 (~QSPI_CS), R5.1, R11.1, U1.1 (SSEL)
QSPI_DATA[0]: IC1.53 (QSPI_SD0), U1.5 (MOSI)
QSPI_DATA[1]: IC1.55 (QSPI_SD1), U1.2 (MISO)
QSPI_DATA[2]: IC1.54 (QSPI_SD2), U1.3 (WP#/IO2)
QSPI_DATA[3]: IC1.51 (QSPI_SD3), U1.7 (HOLD#/IO3)
QSPI_SCK: IC1.52 (QSPI_SCLK), U1.6 (SCK)
RX: IC1.3 (GPIO1), JP1.3
SCK: IC1.17 (GPIO14), JP1.6
SCL: CONN1.4 (SCL), IC1.5 (GPIO3), IC4.4 (SCL), JP3.11, R14.2
SDA: CONN1.3 (SDA), IC1.4 (GPIO2), IC4.6 (SDA), JP3.12, R15.2
SERVO: IC1.31 (GPIO20), SERVO0.1
SWCLK: IC1.24 (SWCLK)
SWDIO: IC1.25 (SWDIO)
TX: IC1.2 (GPIO0), JP1.2
USBBOOT: D3.C, IC1.9 (GPIO7), SW2.A, SW2.A' (P1), TP3.P$1
USB_D+: D+1.TP, R10.1, X6.A6 (D+), X6.B6 (D+)
USB_D-: D-1.TP, R9.1, X6.A7 (D-), X6.B7 (D-)
V+: C16.1, C19.1, GAIN0.3, IC2.5 (VCC), OUTPUTS0.3, Q1.3 (D), R18.2, SERVO0.2, U4.7 (VDD), U4.8 (VDD)
VBAT: C20.1, CHG_EN0.2, JP3.1, Q3.3 (D), X1.2
VBUS: CHG0.A, D4.A, JP3.3, Q3.1 (G), R4.2, U3.4 (VDD), X6.A4B9 (VBUS), X6.B4A9 (VBUS)
VHI: C1.1, D4.C, Q1.2 (S), Q3.2 (S), R3.2, R16.2, U2.1 (IN)
VO+: C22.1, FB1.2, OUTPUTS0.6
VO-: C21.1, FB2.2, OUTPUTS0.5
~ENABLE: Q1.1 (G), Q2.3 (D), R16.1
~RESET: IC1.26 (/RUN), JP1.16, R1.2, SW1.A, SW1.A' (P1)

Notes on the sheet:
Gain=9dB
10K = 100mA
RED LED
USB TYPE C
R1 Channel Selection: LEFT = VDD (0 Ohm) RIGHT = 370K (94*VDD-100) LEFT/2 + RIGHT/2 = 1.011M (222.2*VDD-100)
5.0K = 200mA
USB AND BATTERY CHARGING
1.0K = 1000mA
2.0K = 500mA
RESET
POWER AND FILTERING
NEOPIXEL
BREAKOUTS
RP2040 BYPASS CAPS
QSPI STORAGE
